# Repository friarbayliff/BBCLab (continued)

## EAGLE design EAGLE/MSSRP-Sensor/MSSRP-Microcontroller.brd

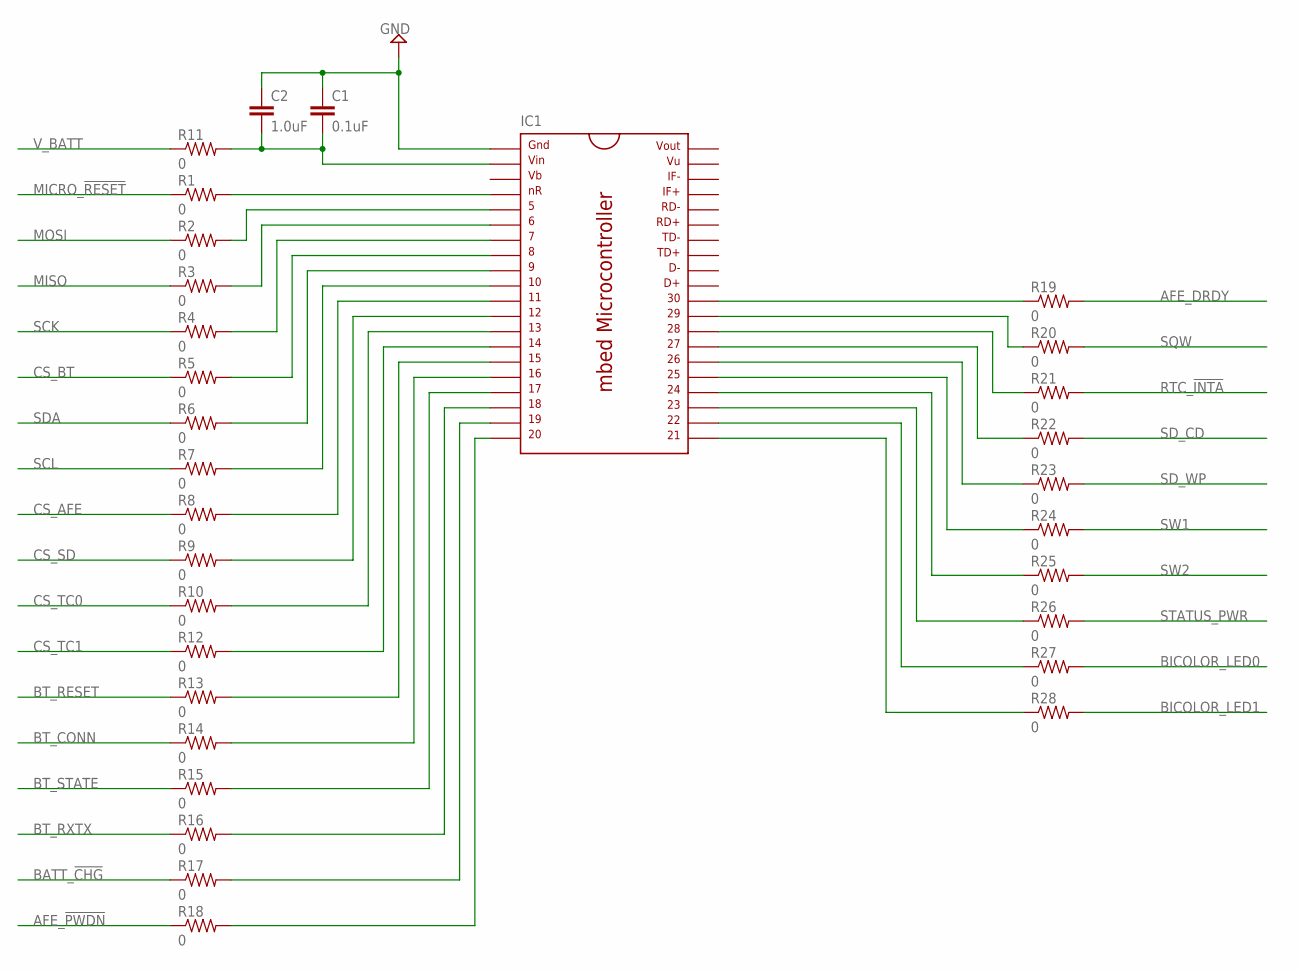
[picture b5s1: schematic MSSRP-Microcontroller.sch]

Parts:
C1: 0.1uF; 0603-CAP
C2: 1.0uF; 0603-CAP
IC1: MBED; DIL40_0.9
R1, R2, R3, R4, R5, R6, R7, R8, R9, R10, R11, R12, R13, R14, R15, R16, R17, R18, R19, R20, R21, R22, R23, R24, R25, R26, R27, R28: 0; 0603

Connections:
AFE_!PWDN: R18.1
AFE_DRDY: R19.2
BATT_!CHG: R17.1
BICOLOR_LED0: R27.2
BICOLOR_LED1: R28.2
BT_CONN: R14.1
BT_RESET: R13.1
BT_RXTX: R16.1
BT_STATE: R15.1
CS_AFE: R8.1
CS_BT: R5.1
CS_SD: R9.1
CS_TC0: R10.1
CS_TC1: R12.1
GND: C1.1, C2.1, IC1.1
MICRO_!RESET: R1.1
MISO: R3.1
MOSI: R2.1
unnamed: IC1.4, R1.2
unnamed: IC1.5, R2.2
unnamed: IC1.6, R3.2
unnamed: IC1.7, R4.2
unnamed: IC1.8, R5.2
unnamed: IC1.9, R6.2
unnamed: IC1.10, R7.2
unnamed: C1.2, C2.2, IC1.2, R11.2
unnamed: IC1.11, R8.2
unnamed: IC1.12, R9.2
unnamed: IC1.13, R10.2
unnamed: IC1.14, R12.2
unnamed: IC1.30, R19.1
unnamed: IC1.15, R13.2
unnamed: IC1.29, R20.1
unnamed: IC1.28, R21.1
unnamed: IC1.27, R22.1
unnamed: IC1.26, R23.1
unnamed: IC1.25, R24.1
unnamed: IC1.16, R14.2
unnamed: IC1.17, R15.2
unnamed: IC1.18, R16.2
unnamed: IC1.19, R17.2
unnamed: IC1.20, R18.2
unnamed: IC1.24, R25.1
unnamed: IC1.23, R26.1
unnamed: IC1.22, R27.1
unnamed: IC1.21, R28.1
RTC_!INTA: R21.2
SCK: R4.1
SCL: R7.1
SDA: R6.1
SD_CD: R22.2
SD_WP: R23.2
SQW: R20.2
STATUS_PWR: R26.2
SW1: R24.2
SW2: R25.2
V_BATT: R11.1

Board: 2 copper layers, 31 parts (0 on the bottom side), 29 nets, no tracks yet.

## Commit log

2014-06-04 second commit - adding schematic files
2014-06-04 added Bluetooth and RTC schematics
2014-06-13 Update 3
    Added Main Board Files
2014-06-13 Ignore list
    Updated Git ignore list and AFE subsystem files
2014-06-13 Layout start
    Some schematic changes, eliminating several 0-ohm “oops” resistors.
    General layout OK, initial routing started.
2014-06-13 Updated routing
    Schematic and routing edits. Core power routing done.
2014-06-16 Routing Update - 2-layer
    Finished 4-layer route. Added 2-layer routing attempt for cost savings.
2014-06-16 Git Ignore
    Updated Git ignore list
2014-06-17 2-layer routing
    Finished 2-layer routing tasks
2014-06-17 Final Beta
    Finished schematic checks and routing adjustments. Boards ready for
    initial CAM.
2014-06-18 DRC and Power pin
    Adjustments to pass DRC: miscellaneous clearance issues and
    double-drill issue with dual connector footprint.
    Also added pin header connection (JP1) to VSYS as a battery system
    bypass option for testing.
2014-06-18 Layer 49
    Added 6 mil outline on layer 49 to export as board outline for 3D
    modeling.
2014-06-18 Final adjustments
    Silkscreen cleanup and minor adjustments before final submission to the
    board house.
2014-06-19 Minor tweaks
    Minor visual tweaks to the schematic file
2014-06-30 Minor changes
2014-07-03 Lite Version
    Added stripped-down ‘lite’ version of the board targeting temperature
    and humidity sensing only
2014-07-03 Final Routing
    Final routing complete
